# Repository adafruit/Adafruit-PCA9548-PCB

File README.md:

## Adafruit PCA9548 8-Channel STEMMA QT I2C Multiplexer PCB

<a href="http://www.adafruit.com/products/5626"><br/>
Click here to purchase one from the Adafruit shop</a>

PCB files for the Adafruit PCA9548 8-Channel STEMMA QT I2C Multiplexer. 

Format is EagleCAD schematic and board layout
* https://www.adafruit.com/product/5626

### Description

You just found the perfect I2C sensor, available in a handy chainable Qwiic, or STEMMA QT package, and you want to wire up two or three or more of them to your microcontroller when you realize "Uh oh, this chip has a fixed I2C address, and from what I know about I2C, you cannot have two devices with the same address on the same SDA/SCL pins!" Are you out of luck? You would be, if you didn't have this ultra-cool Adafruit PCA9548 8 Channel STEMMA QT / Qwiic I2C Multiplexer!

Finally, a way to get up to 8 same-address I2C devices hooked up to one microcontroller - this multiplexer acts as a gatekeeper, shuttling the commands to the selected I2C port with your command.

In case you're wondering why this uses the PCA9548A not the TCA9548A, the PCA9548 is the 'fraternal twin sister' of the TCA9548 but is easier to get during the great chip shortage of 2022. It works exactly the same, just can't go down to 1.8V power which is OK because QT boards are 3V or 5V only anyways. You can still use any example code or library for the TCA9548

Using it is fairly straight-forward: the multiplexer itself is on I2C address 0x70 (but can be adjusted from 0x70 to 0x77 using jumpers on the back) and you simply write a single byte with the desired multiplexed output number to that port, and bam - any future I2C packets will get sent to that port. In theory, you could have 8 of these multiplexers on each of 0x70-0x77 addresses in order to control 64 of the same-I2C-addressed-part.

The Adafruit STEMMA QT / Qwiic PCA9548A Mux Breakout - 8 Channel has eight JST SH 1mm connectors in two rows of four, all with the power, ground, and SDA/SCL pins connected. There's one port at the end that connects to your I2C controller (there are also breadboard breakout pins if you need them). Use this breakout to add as many I2C devices to the bus as you need. Complete with mounting holes so the board can be added to any system. A small power LED lets you know that the hub board has connectivity.

There's even an onboard 3.3V 500mA regulator, so if you're using this with a 5V microcontroler like an Arduino 328-compatible, you can level shift all the QT ports to have 3V power and logic level.

Of course, because STEMMA QT is Qwiic compatible, it will work with any and all STEMMA QT or Qwiic boards and parts we have in the Adafruit shop.

Comes with only the assembled PCB, no cables or sensors included (we have tons available though!)

### License

Adafruit invests time and resources providing this open source design, please support Adafruit and open-source hardware by purchasing products from [Adafruit](https://www.adafruit.com)!

Designed by Limor Fried/Ladyada for Adafruit Industries.

Creative Commons Attribution/Share-Alike, all text above must be included in any redistribution. 
See license.txt for additional details.

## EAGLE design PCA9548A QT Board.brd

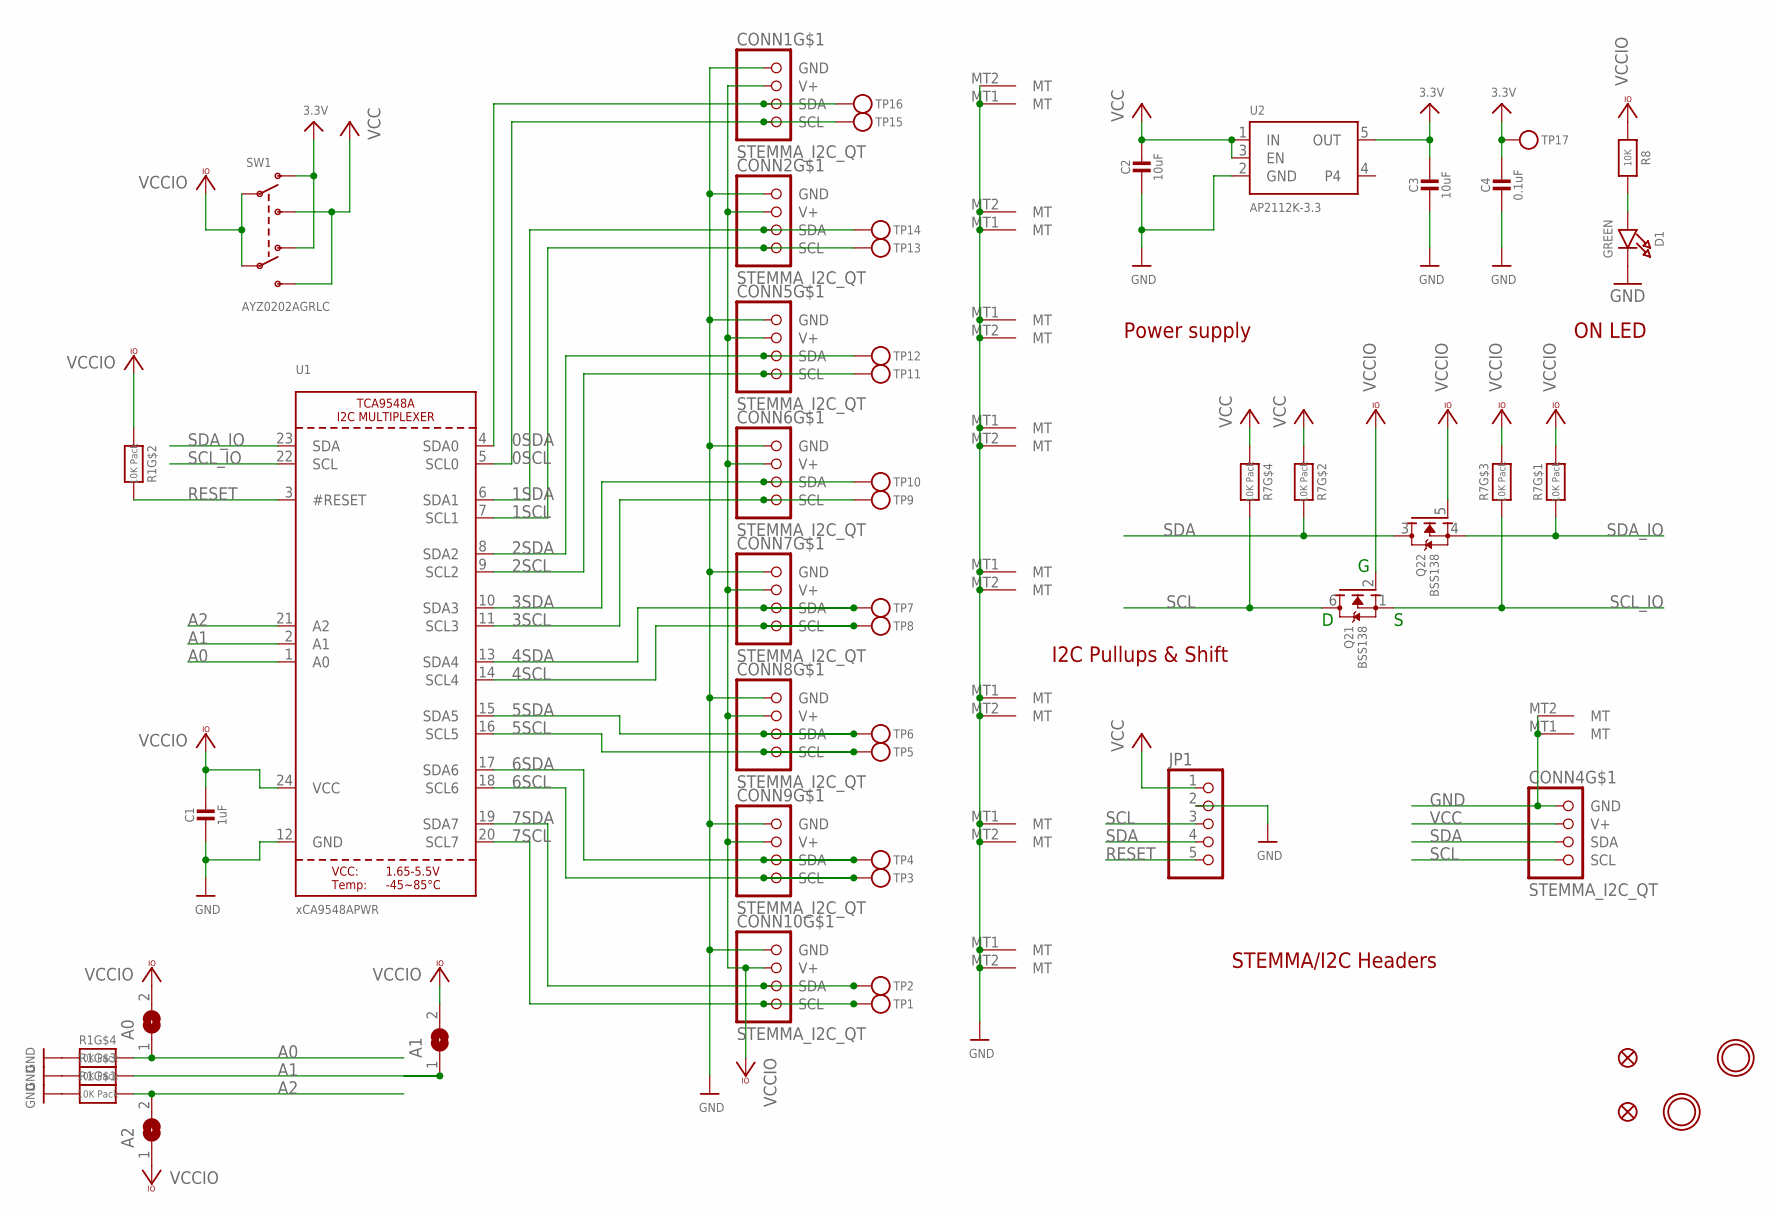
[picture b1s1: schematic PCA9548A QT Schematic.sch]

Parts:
A0, A1, A2: SOLDERJUMPER; SOLDERJUMPER_ARROW_NOPASTE
C1: 1uF; 0603-NO
C2, C3: 10uF; 0805-NO
C4: 0.1uF; 0603-NO
CONN1, CONN2, CONN4, CONN5, CONN6, CONN7, CONN8, CONN9, CONN10: STEMMA_I2C_QT; JST_SH4
D1: GREEN; CHIPLED_0603_NOOUTLINE
FID2, FID4: FIDUCIAL_1MM
JP1: HEADER-1X570MIL; 1X05_ROUND_70
Q2: BSS138; SOT363
R1, R7: 10K Pack; RESPACK_4X0603
R8: 10K; 0603-NO
SW1: AYZ0202AGRLC; EG1390
TP1, TP2, TP3, TP4, TP5, TP6, TP7, TP8, TP9, TP10, TP11, TP12, TP13, TP14, TP15, TP16, TP17: TESTPOINTROUND1.5MMNO; TESTPOINT_ROUND_1.5MM_NO
U1: xCA9548APWR; TSSOP24
U2: AP2112K-3.3; SOT23-5; JLC_ROTATION 0
U$19, U$22: MOUNTINGHOLE2.5; MOUNTINGHOLE_2.5_PLATED

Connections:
0SCL: CONN1.4 (SCL), TP15.P$1, U1.5 (SCL0)
0SDA: CONN1.3 (SDA), TP16.P$1, U1.4 (SDA0)
1SCL: CONN2.4 (SCL), TP13.P$1, U1.7 (SCL1)
1SDA: CONN2.3 (SDA), TP14.P$1, U1.6 (SDA1)
2SCL: CONN5.4 (SCL), TP11.P$1, U1.9 (SCL2)
2SDA: CONN5.3 (SDA), TP12.P$1, U1.8 (SDA2)
3.3V: C3.1, C4.1, SW1.O1, SW1.O2, TP17.P$1, U2.5 (OUT)
3SCL: CONN6.4 (SCL), TP9.P$1, U1.11 (SCL3)
3SDA: CONN6.3 (SDA), TP10.P$1, U1.10 (SDA3)
4SCL: CONN7.4 (SCL), TP8.P$1, U1.14 (SCL4)
4SDA: CONN7.3 (SDA), TP7.P$1, U1.13 (SDA4)
5SCL: CONN8.4 (SCL), TP5.P$1, U1.16 (SCL5)
5SDA: CONN8.3 (SDA), TP6.P$1, U1.15 (SDA5)
6SCL: CONN9.4 (SCL), TP3.P$1, U1.18 (SCL6)
6SDA: CONN9.3 (SDA), TP4.P$1, U1.17 (SDA6)
7SCL: CONN10.4 (SCL), TP1.P$1, U1.20 (SCL7)
7SDA: CONN10.3 (SDA), TP2.P$1, U1.19 (SDA7)
A0: A0.1, R1.5 (2), U1.1 (A0)
A1: A1.1, R1.6 (2), U1.2 (A1)
A2: A2.2, R1.8 (2), U1.21 (A2)
GND: C1.2, C2.2, C3.2, C4.2, CONN1.1 (GND), CONN1.MT1 (MT), CONN1.MT2 (MT), CONN2.1 (GND), CONN2.MT1 (MT), CONN2.MT2 (MT), CONN4.1 (GND), CONN4.MT1 (MT), CONN4.MT2 (MT), CONN5.1 (GND), CONN5.MT1 (MT), CONN5.MT2 (MT), CONN6.1 (GND), CONN6.MT1 (MT), CONN6.MT2 (MT), CONN7.1 (GND), CONN7.MT1 (MT), CONN7.MT2 (MT), CONN8.1 (GND), CONN8.MT1 (MT), CONN8.MT2 (MT), CONN9.1 (GND), CONN9.MT1 (MT), CONN9.MT2 (MT), CONN10.1 (GND), CONN10.MT1 (MT), CONN10.MT2 (MT), D1.C, JP1.2, R1.1, R1.3 (1), R1.4 (1), U1.12 (GND), U2.2 (GND)
unnamed: D1.A, R8.2
RESET: JP1.5, R1.7 (2), U1.3 (#RESET)
SCL: CONN4.4 (SCL), JP1.3, Q2.6 (D), R7.5 (2)
SCL_IO: Q2.1 (S), R7.6 (2), U1.22 (SCL)
SDA: CONN4.3 (SDA), JP1.4, Q2.3 (D), R7.7 (2)
SDA_IO: Q2.4 (S), R7.8 (2), U1.23 (SDA)
VCC: C2.1, CONN4.2 (V+), JP1.1, R7.2 (1), R7.4 (1), SW1.S1, SW1.S2, U2.1 (IN), U2.3 (EN)
VCCIO: A0.2, A1.2, A2.1, C1.1, CONN1.2 (V+), CONN2.2 (V+), CONN5.2 (V+), CONN6.2 (V+), CONN7.2 (V+), CONN8.2 (V+), CONN9.2 (V+), CONN10.2 (V+), Q2.2 (G), Q2.5 (G), R1.2 (1), R7.1, R7.3 (1), R8.1, SW1.P1, SW1.P2, U1.24 (VCC)

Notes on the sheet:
I2C Pullups & Shift
STEMMA/I2C Headers
ON LED
Power supply

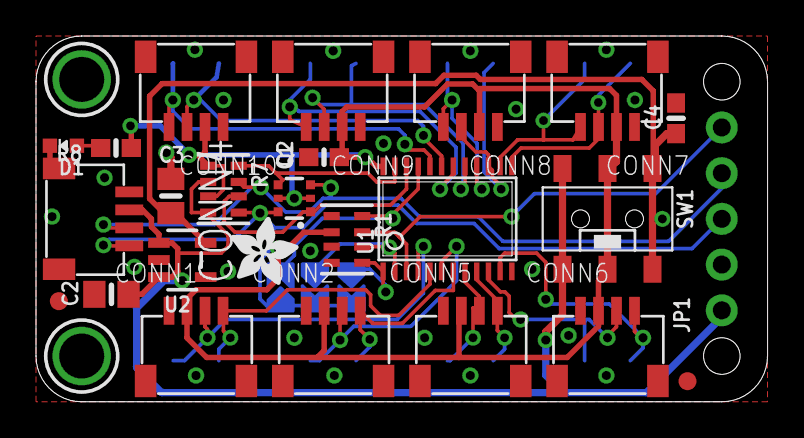
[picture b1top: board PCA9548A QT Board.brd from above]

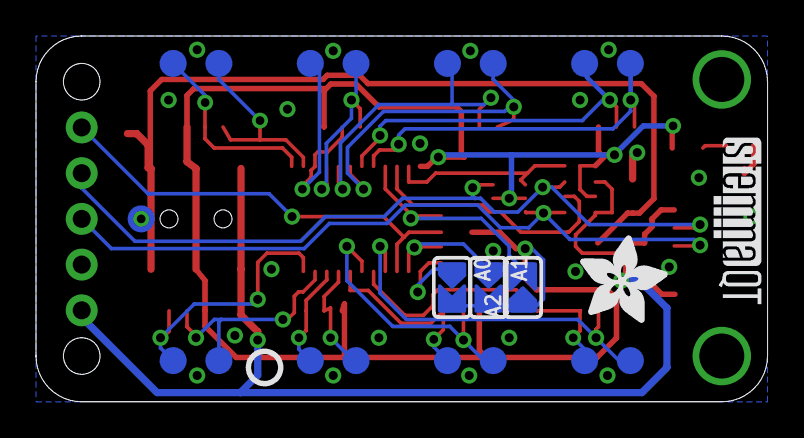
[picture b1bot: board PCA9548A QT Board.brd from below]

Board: 2 copper layers, 40.6 x 20.3 mm, 75 parts (28 on the bottom side), 29 nets.

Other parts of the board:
PLABEL0: PLABEL0
PLABEL1: PLABEL1
PLABEL2: PLABEL2
PLABEL3: PLABEL3
PLABEL4: PLABEL4
PLABEL5: PLABEL5
PLABEL6: PLABEL6
PLABEL7: PLABEL7
PLABEL8: PLABEL8
PLABEL9: PLABEL9
PLABEL10: PLABEL10
PLABEL11: PLABEL11
PLABEL12: PLABEL12
PLABEL13: PLABEL13
PLABEL14: PLABEL14
PLABEL15: PLABEL15
PLABEL16: PLABEL16
PLABEL17: PLABEL17
PLABEL18: PLABEL18
PLABEL19: PLABEL19
PLABEL20: PLABEL20
PLABEL21: PLABEL21
PLABEL22: PLABEL22
PLABEL23: PLABEL23
PLABEL24: PLABEL24
U$5: ADAFRUIT_5MM
U$28: ADAFRUIT_3.5MM
U$29: PCBFEAT-REV-040
U$31: STEMMAQT

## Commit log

2022-10-17 updating readme and adding eagle files

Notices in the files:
parts and their libraries:
microbuilder: This work is placed in the public domain, and may be freely used for commercial and non-commercial work with the following conditions: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
